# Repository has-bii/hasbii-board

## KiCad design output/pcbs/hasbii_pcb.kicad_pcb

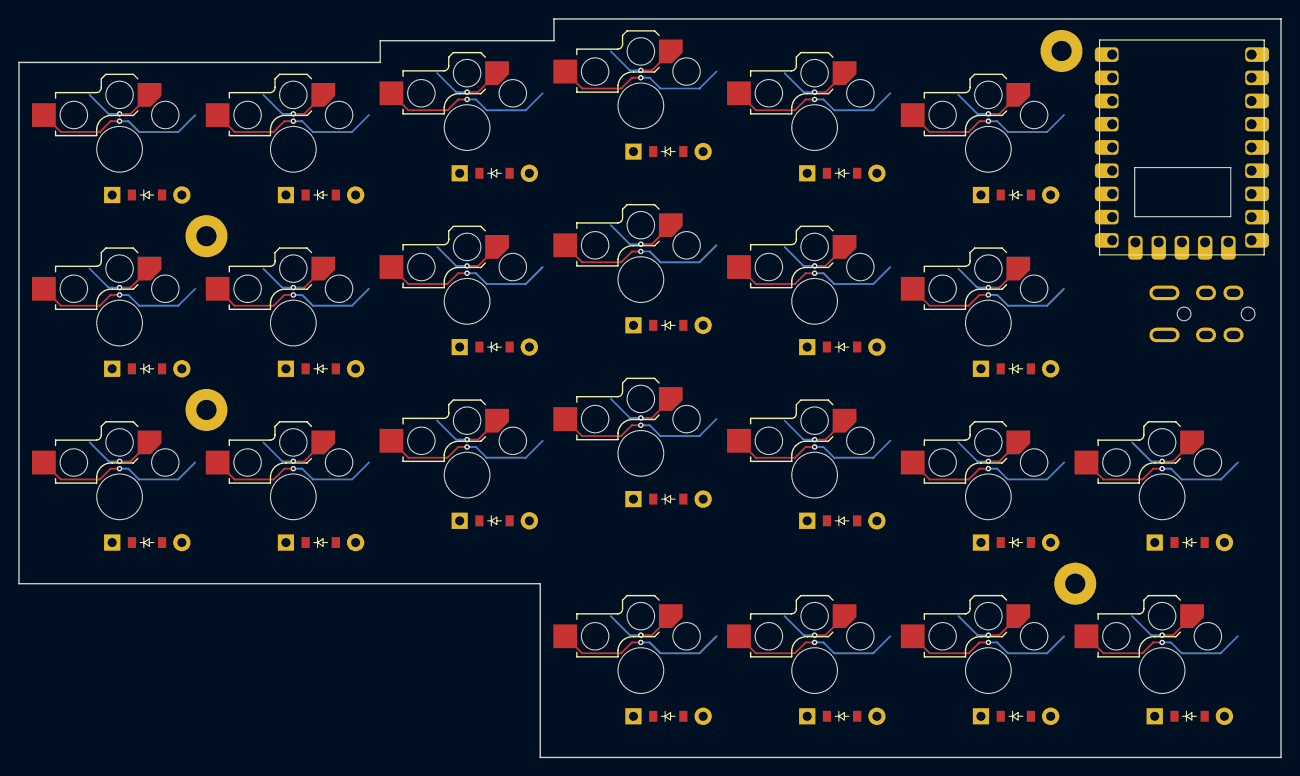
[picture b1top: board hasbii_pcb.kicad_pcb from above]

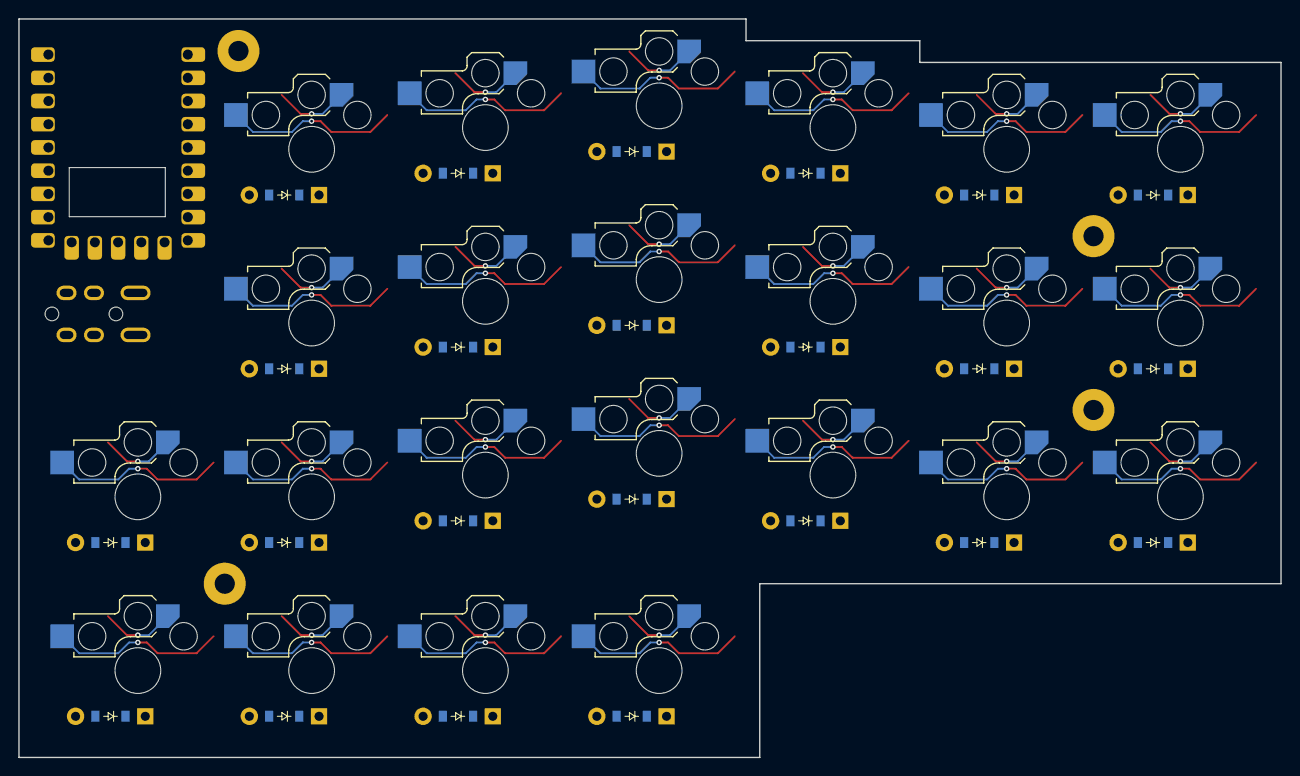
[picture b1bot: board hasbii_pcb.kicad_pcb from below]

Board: 2 copper layers, 138.0 x 80.8 mm, 52 parts (23 on the bottom side), 36 nets.

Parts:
D1, D2, D3, D4, D5, D6, D7, D8, D9, D10, D11, D12, D13, D14, D15, D16, D17, D18, D19, D20, D21, D22, D23: ComboDiode
MH1, MH2, MH3, MH4: mounting_hole_npth
RP2040Zero1: RP2040-Zero
S1, S2, S3, S4, S5, S6, S7, S8, S9, S10, S11, S12, S13, S14, S15, S16, S17, S18, S19, S20, S21, S22, S23: switch_choc_v1_v2
TRRS1: trrs_pj320a (reversible, symmetric)

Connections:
DATA: RP2040Zero1.10, TRRS1.3
GND: RP2040Zero1.20, TRRS1.2
c1: RP2040Zero1.15, S1.1, S2.1, S3.1
c1_r1: D3.2, S3.2
c1_r2: D2.2, S2.2
c1_r3: D1.2, S1.2
c2: RP2040Zero1.16, S4.1, S5.1, S6.1
c2_r1: D6.2, S6.2
c2_r2: D5.2, S5.2
c2_r3: D4.2, S4.2
c3: RP2040Zero1.17, S7.1, S8.1, S9.1, S19.1
c3_r1: D9.2, S9.2
c3_r2: D8.2, S8.2
c3_r3: D7.2, S7.2
c3_r5: D19.2, S19.2
c4: RP2040Zero1.18, S10.1, S11.1, S12.1, S20.1
c4_r1: D12.2, S12.2
c4_r2: D11.2, S11.2
c4_r3: D10.2, S10.2
c4_r5: D20.2, S20.2
c5: RP2040Zero1.22, S13.1, S14.1, S15.1, S21.1
c5_r1: D15.2, S15.2
c5_r2: D14.2, S14.2
c5_r3: D13.2, S13.2
c5_r5: D21.2, S21.2
c6: RP2040Zero1.23, S16.1, S17.1, S18.1, S22.1, S23.1
c6_r1: D18.2, S18.2
c6_r2: D17.2, S17.2
c6_r3: D16.2, S16.2
c6_r4: D23.2, S23.2
c6_r5: D22.2, S22.2
r1: D3.1, D6.1, D9.1, D12.1, D15.1, D18.1, RP2040Zero1.5
r2: D2.1, D5.1, D8.1, D11.1, D14.1, D17.1, RP2040Zero1.8
r3: D1.1, D4.1, D7.1, D10.1, D13.1, D16.1, RP2040Zero1.9
r4: D23.1, RP2040Zero1.13
r5: D19.1, D20.1, D21.1, D22.1, RP2040Zero1.14

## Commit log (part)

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2026-02-23 init
2026-02-23 update keyboard.yaml: adjust unit size and add PCB configurations
2026-02-24 chore: clean up empty code change sections in the changes log
2026-02-24 output
2026-02-24 add footprints
2026-02-24 feat: adjust TRRS anchor shift in config and add new a-dux configuration
2026-02-24 Add top frame outline and extrusion function for case design
    - Implemented `_top_frame_extrude_3_outline_fn` to create the outline of the top frame using CSG.Path2D and CAG operations.
    - Introduced `top_frame_case_fn` to generate the top frame part, including translation and rotation adjustments.
    - Defined a `main` function to return the result of the top frame case function.
